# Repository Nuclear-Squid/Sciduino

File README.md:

# Sciduino

An experiment to replace LabVIEW and NI-DAQ devices by a SciPy + PySide + Arduino stack.

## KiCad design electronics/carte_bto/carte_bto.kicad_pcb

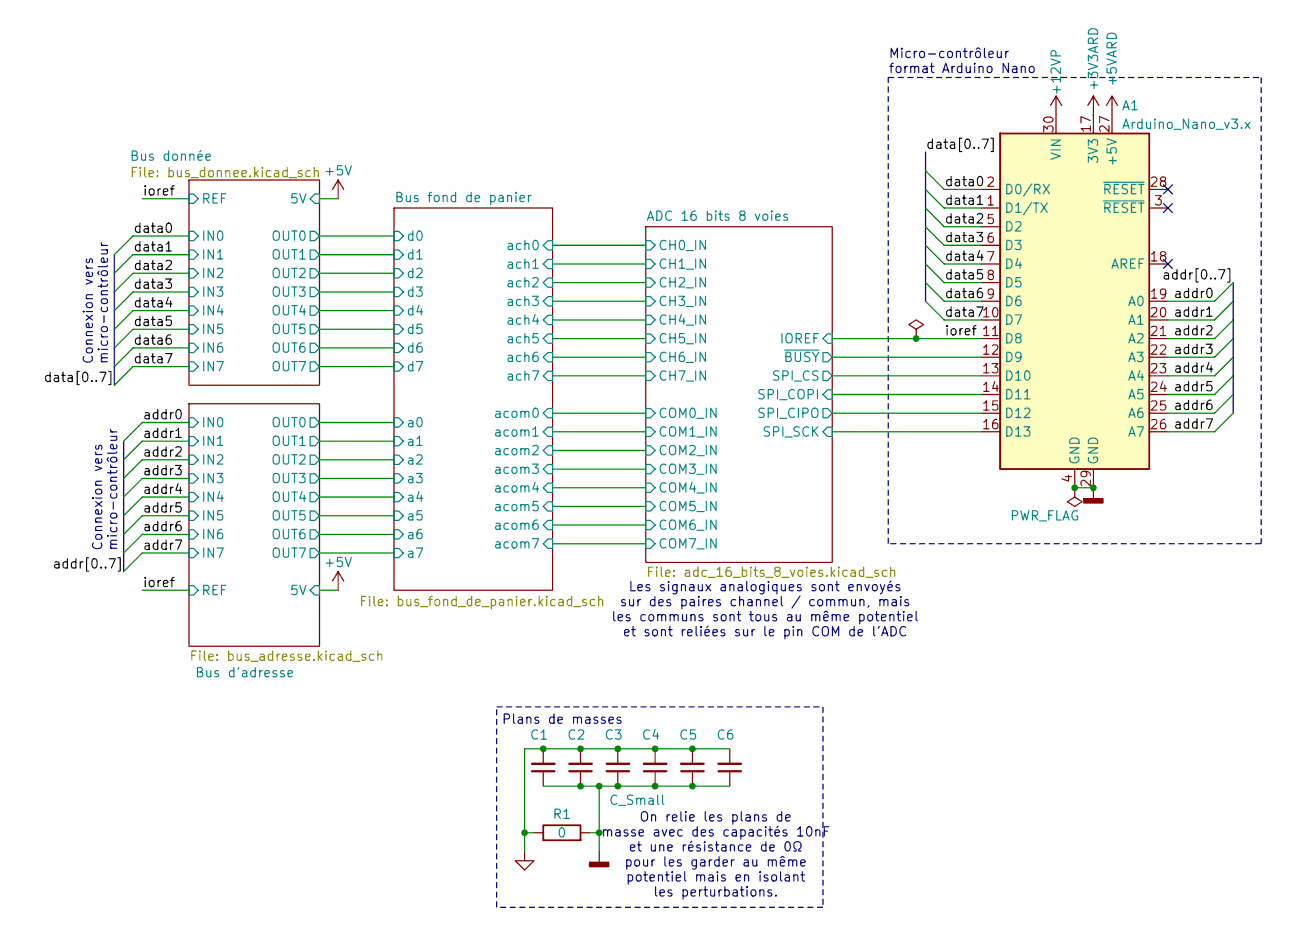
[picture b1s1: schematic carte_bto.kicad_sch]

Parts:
A1: Arduino_Nano_v3.x; Arduino_Nano
C1, C2, C3, C4, C5, C6: C_Small; C_0805_2012Metric_Pad1.18x1.45mm_HandSolder
R1: 0; R_0805_2012Metric_Pad1.20x1.40mm_HandSolder

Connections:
+3V3ARD: A1.17 (3V3)
+5VARD: A1.27 (+5V); also elsewhere on the board
+12VP: A1.30 (VIN); also elsewhere on the board
/ADC 16 bits 8 voies/SPI_CIPO: A1.15 (D12); also elsewhere on the board
/ADC 16 bits 8 voies/SPI_COPI: A1.14 (D11); also elsewhere on the board
/ADC 16 bits 8 voies/SPI_CS: A1.13 (D10); also elsewhere on the board
/ADC 16 bits 8 voies/SPI_SCK: A1.16 (D13); also elsewhere on the board
/ADC 16 bits 8 voies/~BUSY: A1.12 (D9); also elsewhere on the board
/addr0: A1.19 (A0); also elsewhere on the board
/addr1: A1.20 (A1); also elsewhere on the board
/addr2: A1.21 (A2); also elsewhere on the board
/addr3: A1.22 (A3); also elsewhere on the board
/addr4: A1.23 (A4); also elsewhere on the board
/addr5: A1.24 (A5); also elsewhere on the board
/addr6: A1.25 (A6); also elsewhere on the board
/addr7: A1.26 (A7); also elsewhere on the board
/data0: A1.2 (D0/RX); also elsewhere on the board
/data1: A1.1 (D1/TX); also elsewhere on the board
/data2: A1.5 (D2); also elsewhere on the board
/data3: A1.6 (D3); also elsewhere on the board
/data4: A1.7 (D4); also elsewhere on the board
/data5: A1.8 (D5); also elsewhere on the board
/data6: A1.9 (D6); also elsewhere on the board
/data7: A1.10 (D7); also elsewhere on the board
/ioref: A1.11 (D8); also elsewhere on the board
GND1: C1.2, C2.2, C3.2, C4.2, C5.2, C6.2, R1.1; also elsewhere on the board
GND2: A1.4 (GND), A1.29 (GND), C1.1, C2.1, C3.1, C4.1, C5.1, C6.1, R1.2; also elsewhere on the board

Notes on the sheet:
Connexion vers micro-contrôleur
Micro-contrôleur format Arduino Nano
Plans de masses
Les signaux analogiques sont envoyés sur des paires channel / commun, mais les communs sont tous au même potentiel et sont reliées sur le pin COM de l’ADC
On relie les plans de masse avec des capacités 10nF et une résistance de 0Ω pour les garder au même potentiel mais en isolant les perturbations.

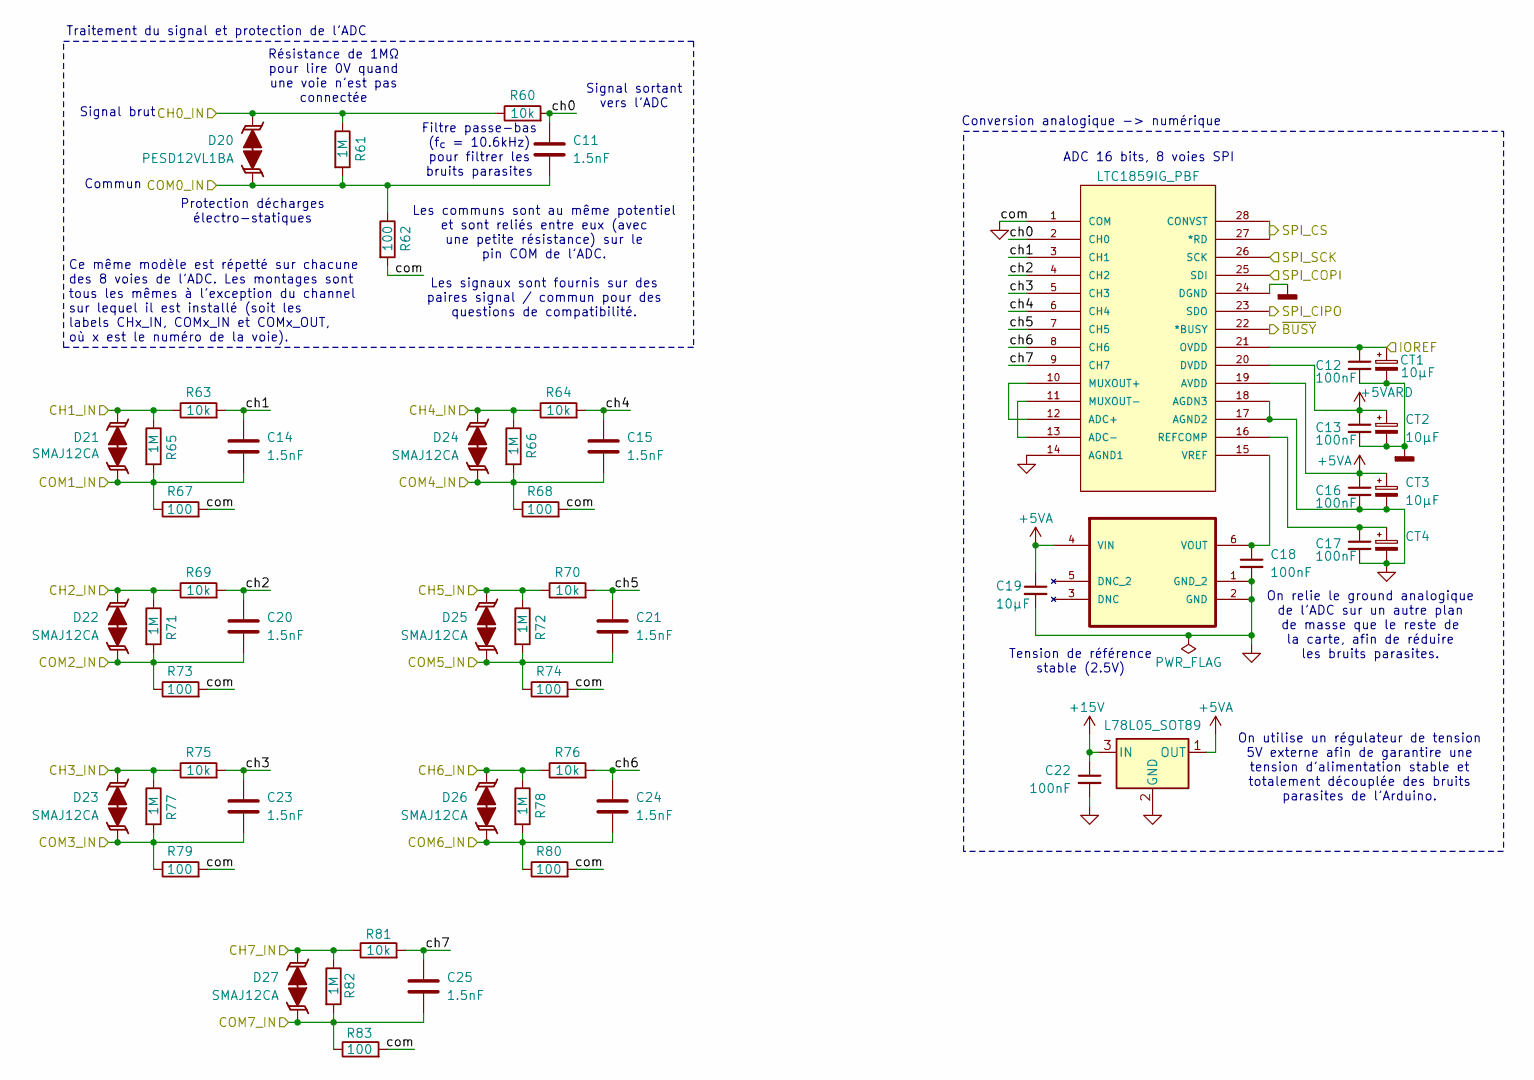
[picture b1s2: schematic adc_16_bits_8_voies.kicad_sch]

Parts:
C11, C14, C15, C20, C21, C23, C24, C25: 1.5nF; C_0805_2012Metric_Pad1.18x1.45mm_HandSolder
C12, C13, C16, C17, C18, C22: 100nF; C_0805_2012Metric_Pad1.18x1.45mm_HandSolder
C19: 10µF; C_0805_2012Metric_Pad1.18x1.45mm_HandSolder
CT1, CT2, CT3, CT4: 10µF; CP_EIA-2012-12_Kemet-R
D20: PESD12VL1BA; D_SOD-323_HandSoldering
D21, D22, D23, D24, D25, D26, D27: SMAJ12CA; D_SOD-323_HandSoldering
R60, R63, R64, R69, R70, R75, R76, R81: 10k; R_0805_2012Metric_Pad1.20x1.40mm_HandSolder
R61, R65, R66, R71, R72, R77, R78, R82: 1M; R_0805_2012Metric_Pad1.20x1.40mm_HandSolder
R62, R67, R68, R73, R74, R79, R80, R83: 100; R_0805_2012Metric_Pad1.20x1.40mm_HandSolder
U3: LTC1859IG_PBF; SSOP-28_G; MANUFACTURER_PART_NUMBER ltc1859ig
U4: LT6654AIS6-2.5_TRPBF; SOT95P280X100-6N; MPN LT6654BHS6-5#TRMPBF
U5: L78L05_SOT89; SOT-89-3_Handsoldering

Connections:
+5VA: C16.1, C19.1, CT3.1, U3.19 (AVDD), U4.4 (VIN), U5.1 (OUT)
+5VARD: C13.1, CT2.1, U3.20 (DVDD); also elsewhere on the board
+15V: C22.1, U5.3 (IN); also elsewhere on the board
/ADC 16 bits 8 voies/CH0_IN: D20.2 (A2), R60.1, R61.1; also elsewhere on the board
/ADC 16 bits 8 voies/CH1_IN: D21.2 (A2), R63.1, R65.1; also elsewhere on the board
/ADC 16 bits 8 voies/CH2_IN: D22.2 (A2), R69.1, R71.1; also elsewhere on the board
/ADC 16 bits 8 voies/CH3_IN: D23.2 (A2), R75.1, R77.1; also elsewhere on the board
/ADC 16 bits 8 voies/CH4_IN: D24.2 (A2), R64.1, R66.1; also elsewhere on the board
/ADC 16 bits 8 voies/CH5_IN: D25.2 (A2), R70.1, R72.1; also elsewhere on the board
/ADC 16 bits 8 voies/CH6_IN: D26.2 (A2), R76.1, R78.1; also elsewhere on the board
/ADC 16 bits 8 voies/CH7_IN: D27.2 (A2), R81.1, R82.1; also elsewhere on the board
/ADC 16 bits 8 voies/COM0_IN: C11.2, D20.1 (A1), R61.2, R62.1; also elsewhere on the board
/ADC 16 bits 8 voies/COM1_IN: C14.2, D21.1 (A1), R65.2, R67.1; also elsewhere on the board
/ADC 16 bits 8 voies/COM2_IN: C20.2, D22.1 (A1), R71.2, R73.1; also elsewhere on the board
/ADC 16 bits 8 voies/COM3_IN: C23.2, D23.1 (A1), R77.2, R79.1; also elsewhere on the board
/ADC 16 bits 8 voies/COM4_IN: C15.2, D24.1 (A1), R66.2, R68.1; also elsewhere on the board
/ADC 16 bits 8 voies/COM5_IN: C21.2, D25.1 (A1), R72.2, R74.1; also elsewhere on the board
/ADC 16 bits 8 voies/COM6_IN: C24.2, D26.1 (A1), R78.2, R80.1; also elsewhere on the board
/ADC 16 bits 8 voies/COM7_IN: C25.2, D27.1 (A1), R82.2, R83.1; also elsewhere on the board
/ADC 16 bits 8 voies/SPI_CIPO: U3.23 (SDO); also elsewhere on the board
/ADC 16 bits 8 voies/SPI_COPI: U3.25 (SDI); also elsewhere on the board
/ADC 16 bits 8 voies/SPI_CS: U3.27 (*RD), U3.28 (CONVST); also elsewhere on the board
/ADC 16 bits 8 voies/SPI_SCK: U3.26 (SCK); also elsewhere on the board
/ADC 16 bits 8 voies/ch0: C11.1, R60.2, U3.2 (CH0)
/ADC 16 bits 8 voies/ch1: C14.1, R63.2, U3.3 (CH1)
/ADC 16 bits 8 voies/ch2: C20.1, R69.2, U3.4 (CH2)
/ADC 16 bits 8 voies/ch3: C23.1, R75.2, U3.5 (CH3)
/ADC 16 bits 8 voies/ch4: C15.1, R64.2, U3.6 (CH4)
/ADC 16 bits 8 voies/ch5: C21.1, R70.2, U3.7 (CH5)
/ADC 16 bits 8 voies/ch6: C24.1, R76.2, U3.8 (CH6)
/ADC 16 bits 8 voies/ch7: C25.1, R81.2, U3.9 (CH7)
/ADC 16 bits 8 voies/~BUSY: U3.22 (*BUSY); also elsewhere on the board
/ioref: C12.1, CT1.1, U3.21 (OVDD); also elsewhere on the board
GND1: C16.2, C17.2, C18.2, C19.2, C22.2, CT3.2, CT4.2, R62.2, R67.2, R68.2, R73.2, R74.2, R79.2, R80.2, R83.2, U3.1 (COM), U3.14 (AGND1), U3.17 (AGND2), U3.18 (AGDN3), U4.1 (GND_2), U4.2 (GND), U5.2 (GND); also elsewhere on the board
GND2: C12.2, C13.2, CT1.2, CT2.2, U3.24 (DGND); also elsewhere on the board
unnamed: U3.10 (MUXOUT+), U3.12 (ADC+)
unnamed: U3.11 (MUXOUT-), U3.13 (ADC-)
unnamed: C17.1, CT4.1, U3.16 (REFCOMP)
unnamed: C18.1, U3.15 (VREF), U4.6 (VOUT)

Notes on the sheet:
Signal sortant vers l’ADC
Traitement du signal et protection de l’ADC
On utilise un régulateur de tension 5V externe afin de garantire une tension d’alimentation stable et totalement découplée des bruits parasites de l’Arduino.
Résistance de 1MΩ pour lire 0V quand une voie n’est pas connectée
ADC 16 bits, 8 voies SPI
Tension de référence stable (2.5V)
Les communs sont au même potentiel et sont reliés entre eux (avec une petite résistance) sur le pin COM de l’ADC. Les signaux sont fournis sur des paires signal / commun pour des questions de compatibilité.
Filtre passe-bas (f_{c} = 10.6kHz) pour filtrer les bruits parasites
Ce même modèle est répetté sur chacune des 8 voies de l’ADC. Les montages sont tous les mêmes à l’exception du channel sur lequel il est installé (soit les labels CHx_IN, COMx_IN et COMx_OUT, où x est le numéro de la voie).
Signal brut
Commun
Conversion analogique -> numérique
On relie le ground analogique de l’ADC sur un autre plan de masse que le reste de la carte, afin de réduire les bruits parasites.
Protection décharges électro-statiques

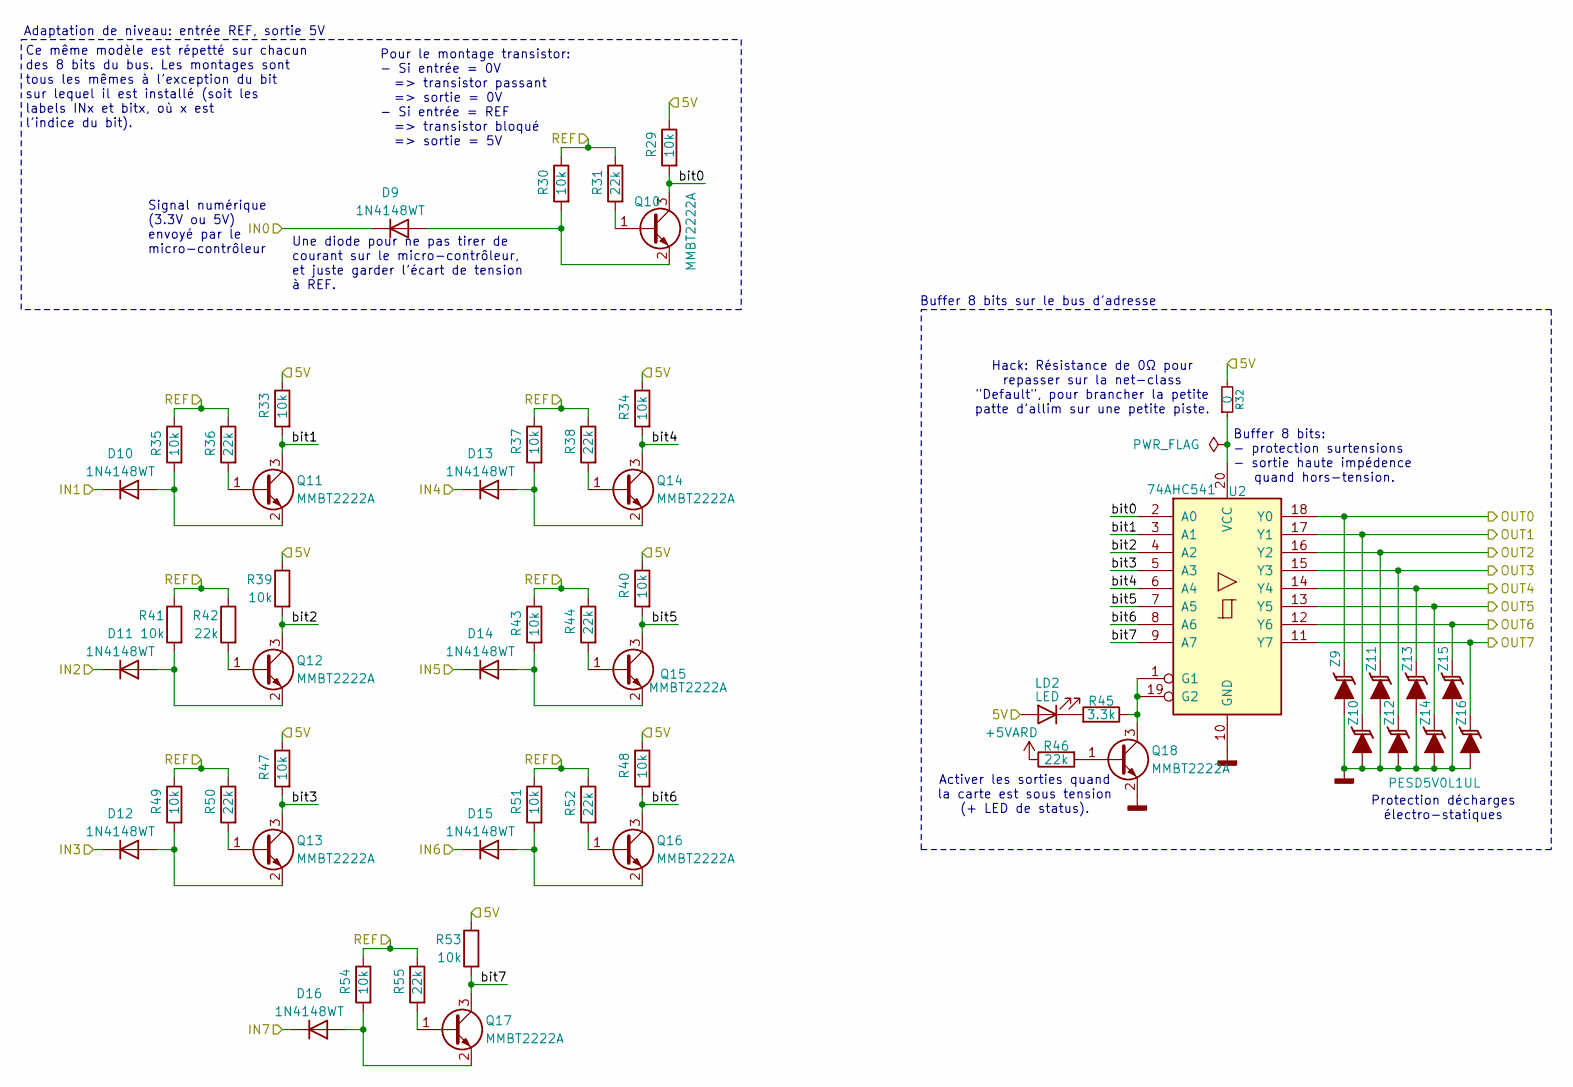
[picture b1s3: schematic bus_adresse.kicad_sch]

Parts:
D9, D10, D11, D12, D13, D14, D15, D16: 1N4148WT; D_SOD-523
LD2: LED; LED_0805_2012Metric_Pad1.15x1.40mm_HandSolder
Q10, Q11, Q12, Q13, Q14, Q15, Q16, Q17, Q18: MMBT2222A; SOT-23_Handsoldering
R29, R30, R33, R34, R35, R37, R39, R40, R41, R43, R47, R48, R49, R51, R53, R54: 10k; R_0805_2012Metric_Pad1.20x1.40mm_HandSolder
R31, R36, R38, R42, R44, R46, R50, R52, R55: 22k; R_0805_2012Metric_Pad1.20x1.40mm_HandSolder
R32: 0; R_0805_2012Metric_Pad1.20x1.40mm_HandSolder
R45: 3.3k; R_0805_2012Metric_Pad1.20x1.40mm_HandSolder
U2: 74AHC541; SOIC-20W_7.5x12.8mm_P1.27mm
Z9, Z10, Z11, Z12, Z13, Z14, Z15, Z16: PESD5V0L1UL; D_SOD-882_DFN1006-2_TVS

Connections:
+5V: LD2.2 (A), R29.1, R32.2, R33.1, R34.1, R39.1, R40.1, R47.1, R48.1, R53.1; also elsewhere on the board
+5VARD: R46.1; also elsewhere on the board
/Bus d’adresse/OUT0: U2.18 (Y0), Z9.1 (K); also elsewhere on the board
/Bus d’adresse/OUT1: U2.17 (Y1), Z10.1 (K); also elsewhere on the board
/Bus d’adresse/OUT2: U2.16 (Y2), Z11.1 (K); also elsewhere on the board
/Bus d’adresse/OUT3: U2.15 (Y3), Z12.1 (K); also elsewhere on the board
/Bus d’adresse/OUT4: U2.14 (Y4), Z13.1 (K); also elsewhere on the board
/Bus d’adresse/OUT5: U2.13 (Y5), Z14.1 (K); also elsewhere on the board
/Bus d’adresse/OUT6: U2.12 (Y6), Z15.1 (K); also elsewhere on the board
/Bus d’adresse/OUT7: U2.11 (Y7), Z16.1 (K); also elsewhere on the board
/Bus d’adresse/bit0: Q10.3 (C), R29.2, U2.2 (A0)
/Bus d’adresse/bit1: Q11.3 (C), R33.2, U2.3 (A1)
/Bus d’adresse/bit2: Q12.3 (C), R39.2, U2.4 (A2)
/Bus d’adresse/bit3: Q13.3 (C), R47.2, U2.5 (A3)
/Bus d’adresse/bit4: Q14.3 (C), R34.2, U2.6 (A4)
/Bus d’adresse/bit5: Q15.3 (C), R40.2, U2.7 (A5)
/Bus d’adresse/bit6: Q16.3 (C), R48.2, U2.8 (A6)
/Bus d’adresse/bit7: Q17.3 (C), R53.2, U2.9 (A7)
/addr0: D9.1 (K); also elsewhere on the board
/addr1: D10.1 (K); also elsewhere on the board
/addr2: D11.1 (K); also elsewhere on the board
/addr3: D12.1 (K); also elsewhere on the board
/addr4: D13.1 (K); also elsewhere on the board
/addr5: D14.1 (K); also elsewhere on the board
/addr6: D15.1 (K); also elsewhere on the board
/addr7: D16.1 (K); also elsewhere on the board
/ioref: R30.1, R31.1, R35.1, R36.1, R37.1, R38.1, R41.1, R42.1, R43.1, R44.1, R49.1, R50.1, R51.1, R52.1, R54.1, R55.1; also elsewhere on the board
GND2: Q18.2 (E), U2.10 (GND), Z9.2 (A), Z10.2 (A), Z11.2 (A), Z12.2 (A), Z13.2 (A), Z14.2 (A), Z15.2 (A), Z16.2 (A); also elsewhere on the board
unnamed: D9.2 (A), Q10.2 (E), R30.2
unnamed: D10.2 (A), Q11.2 (E), R35.2
unnamed: D11.2 (A), Q12.2 (E), R41.2
unnamed: D12.2 (A), Q13.2 (E), R49.2
unnamed: D13.2 (A), Q14.2 (E), R37.2
unnamed: D14.2 (A), Q15.2 (E), R43.2
unnamed: D15.2 (A), Q16.2 (E), R51.2
unnamed: D16.2 (A), Q17.2 (E), R54.2
unnamed: LD2.1 (K), R45.2
unnamed: Q10.1 (B), R31.2
unnamed: Q11.1 (B), R36.2
unnamed: Q12.1 (B), R42.2
unnamed: Q13.1 (B), R50.2
unnamed: Q14.1 (B), R38.2
unnamed: Q15.1 (B), R44.2
unnamed: Q16.1 (B), R52.2
unnamed: Q17.1 (B), R55.2
unnamed: Q18.1 (B), R46.2
unnamed: Q18.3 (C), R45.1, U2.1 (G1), U2.19 (G2)
unnamed: R32.1, U2.20 (VCC)

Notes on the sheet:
Buffer 8 bits: - protection surtensions - sortie haute impédence quand hors-tension.
Une diode pour ne pas tirer de courant sur le micro-contrôleur, et juste garder l’écart de tension à REF.
Ce même modèle est répetté sur chacun des 8 bits du bus. Les montages sont tous les mêmes à l’exception du bit sur lequel il est installé (soit les labels INx et bitx, où x est l’indice du bit).
Activer les sorties quand la carte est sous tension (+ LED de status).
Adaptation de niveau: entrée REF, sortie 5V
Hack: Résistance de 0Ω pour repasser sur la net-class "Default", pour brancher la petite patte d’allim sur une petite piste.
Signal numérique (3.3V ou 5V) envoyé par le micro-contrôleur
Buffer 8 bits sur le bus d’adresse
Pour le montage transistor: - Si entrée = 0V => transistor passant => sortie = 0V - Si entrée = REF => transistor bloqué => sortie = 5V
Protection décharges électro-statiques

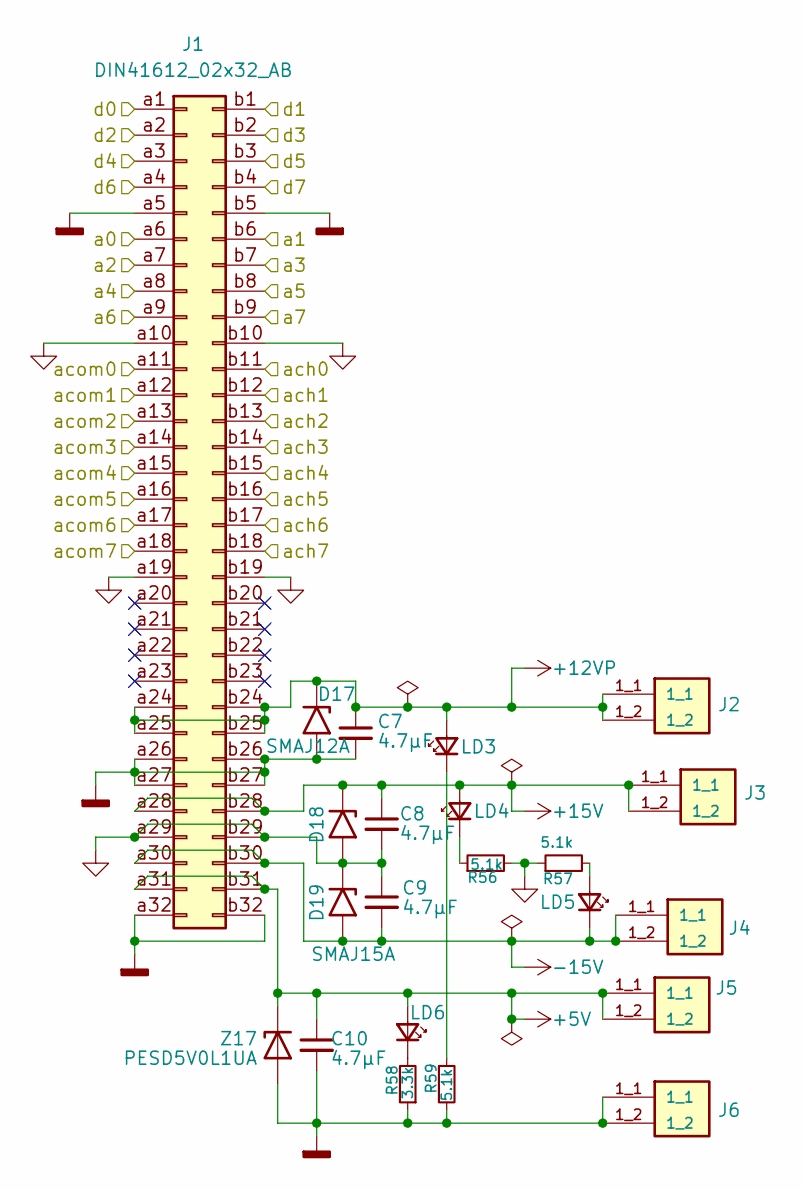
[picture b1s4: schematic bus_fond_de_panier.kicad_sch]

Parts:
C7, C8, C9, C10: 4.7µF; C_0805_2012Metric_Pad1.18x1.45mm_HandSolder
D17: SMAJ12A; D_SOD-323_HandSoldering
D18, D19: SMAJ15A; D_SOD-323_HandSoldering
J1: DIN41612_02x32_AB; DIN41612_B_2x32_Male_Horizontal_THT
J2, J3, J4, J5, J6: Conn_01x01; HIRSCHMANN_930224100
LD3, LD4, LD5, LD6: LED_Small; LED_0805_2012Metric_Pad1.15x1.40mm_HandSolder
R56, R57, R59: 5.1k; R_0805_2012Metric_Pad1.20x1.40mm_HandSolder
R58: 3.3k; R_0805_2012Metric_Pad1.20x1.40mm_HandSolder
Z17: PESD5V0L1UA; D_SOD-323_HandSoldering

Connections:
+5V: C10.1, J1.a31, J1.b31, J5.1_1, J5.1_2, LD6.2 (A), Z17.1 (K); also elsewhere on the board
+12VP: C7.1, D17.1 (A1), J1.a24, J1.a25, J1.b24, J1.b25, J2.1_1, J2.1_2, LD3.2 (A); also elsewhere on the board
+15V: C8.1, D18.1 (A1), J1.a28, J1.b28, J3.1_1, J3.1_2, LD4.2 (A); also elsewhere on the board
-15V: C9.2, D19.2 (A2), J1.a30, J1.b30, J4.1_1, J4.1_2, LD5.1 (K)
/ADC 16 bits 8 voies/CH0_IN: J1.b11; also elsewhere on the board
/ADC 16 bits 8 voies/CH1_IN: J1.b12; also elsewhere on the board
/ADC 16 bits 8 voies/CH2_IN: J1.b13; also elsewhere on the board
/ADC 16 bits 8 voies/CH3_IN: J1.b14; also elsewhere on the board
/ADC 16 bits 8 voies/CH4_IN: J1.b15; also elsewhere on the board
/ADC 16 bits 8 voies/CH5_IN: J1.b16; also elsewhere on the board
/ADC 16 bits 8 voies/CH6_IN: J1.b17; also elsewhere on the board
/ADC 16 bits 8 voies/CH7_IN: J1.b18; also elsewhere on the board
/ADC 16 bits 8 voies/COM0_IN: J1.a11; also elsewhere on the board
/ADC 16 bits 8 voies/COM1_IN: J1.a12; also elsewhere on the board
/ADC 16 bits 8 voies/COM2_IN: J1.a13; also elsewhere on the board
/ADC 16 bits 8 voies/COM3_IN: J1.a14; also elsewhere on the board
/ADC 16 bits 8 voies/COM4_IN: J1.a15; also elsewhere on the board
/ADC 16 bits 8 voies/COM5_IN: J1.a16; also elsewhere on the board
/ADC 16 bits 8 voies/COM6_IN: J1.a17; also elsewhere on the board
/ADC 16 bits 8 voies/COM7_IN: J1.a18; also elsewhere on the board
/Bus donnée/OUT0: J1.a1; also elsewhere on the board
/Bus donnée/OUT1: J1.b1; also elsewhere on the board
/Bus donnée/OUT2: J1.a2; also elsewhere on the board
/Bus donnée/OUT3: J1.b2; also elsewhere on the board
/Bus donnée/OUT4: J1.a3; also elsewhere on the board
/Bus donnée/OUT5: J1.b3; also elsewhere on the board
/Bus donnée/OUT6: J1.a4; also elsewhere on the board
/Bus donnée/OUT7: J1.b4; also elsewhere on the board
/Bus d’adresse/OUT0: J1.a6; also elsewhere on the board
/Bus d’adresse/OUT1: J1.b6; also elsewhere on the board
/Bus d’adresse/OUT2: J1.a7; also elsewhere on the board
/Bus d’adresse/OUT3: J1.b7; also elsewhere on the board
/Bus d’adresse/OUT4: J1.a8; also elsewhere on the board
/Bus d’adresse/OUT5: J1.b8; also elsewhere on the board
/Bus d’adresse/OUT6: J1.a9; also elsewhere on the board
/Bus d’adresse/OUT7: J1.b9; also elsewhere on the board
GND1: C8.2, C9.1, D18.2 (A2), D19.1 (A1), J1.a10, J1.a19, J1.a29, J1.b10, J1.b19, J1.b29, R56.2, R57.1; also elsewhere on the board
GND2: C7.2, C10.2, D17.2 (A2), J1.a5, J1.a26, J1.a27, J1.a32, J1.b5, J1.b26, J1.b27, J1.b32, J6.1_1, J6.1_2, R58.1, R59.2, Z17.2 (A); also elsewhere on the board
unnamed: LD3.1 (K), R59.1
unnamed: LD4.1 (K), R56.1
unnamed: LD5.2 (A), R57.2
unnamed: LD6.1 (K), R58.2

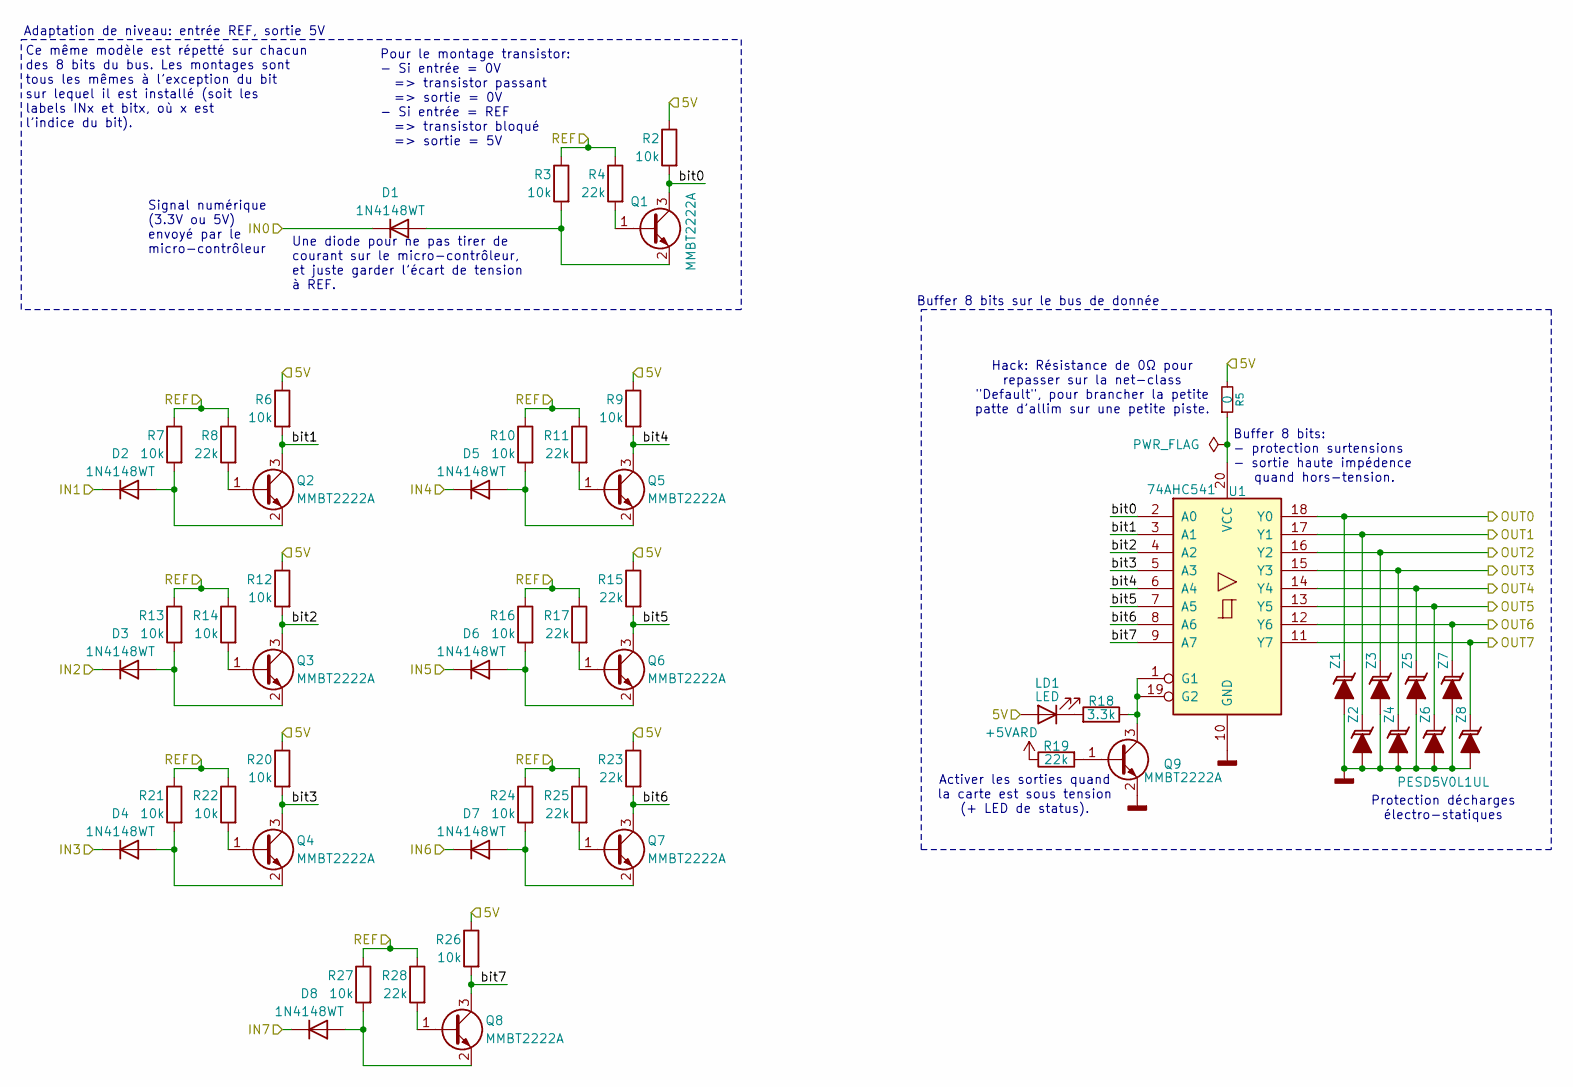
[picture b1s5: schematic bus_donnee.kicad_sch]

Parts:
D1, D2, D3, D4, D5, D6, D7, D8: 1N4148WT; D_SOD-523
LD1: LED; LED_0805_2012Metric_Pad1.15x1.40mm_HandSolder
Q1, Q2, Q3, Q4, Q5, Q6, Q7, Q8, Q9: MMBT2222A; SOT-23_Handsoldering
R2, R3, R6, R7, R9, R10, R12, R13, R14, R16, R20, R21, R22, R24, R26, R27: 10k; R_0805_2012Metric_Pad1.20x1.40mm_HandSolder
R4, R8, R11, R15, R17, R19, R23, R25, R28: 22k; R_0805_2012Metric_Pad1.20x1.40mm_HandSolder
R5: 0; R_0805_2012Metric_Pad1.20x1.40mm_HandSolder
R18: 3.3k; R_0805_2012Metric_Pad1.20x1.40mm_HandSolder
U1: 74AHC541; SOIC-20W_7.5x12.8mm_P1.27mm
Z1, Z2, Z3, Z4, Z5, Z6, Z7, Z8: PESD5V0L1UL; D_SOD-882_DFN1006-2_TVS

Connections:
+5V: LD1.2 (A), R2.1, R5.2, R6.1, R9.1, R12.1, R15.1, R20.1, R23.1, R26.1; also elsewhere on the board
+5VARD: R19.1; also elsewhere on the board
/Bus donnée/OUT0: U1.18 (Y0), Z1.1 (K); also elsewhere on the board
/Bus donnée/OUT1: U1.17 (Y1), Z2.1 (K); also elsewhere on the board
/Bus donnée/OUT2: U1.16 (Y2), Z3.1 (K); also elsewhere on the board
/Bus donnée/OUT3: U1.15 (Y3), Z4.1 (K); also elsewhere on the board
/Bus donnée/OUT4: U1.14 (Y4), Z5.1 (K); also elsewhere on the board
/Bus donnée/OUT5: U1.13 (Y5), Z6.1 (K); also elsewhere on the board
/Bus donnée/OUT6: U1.12 (Y6), Z7.1 (K); also elsewhere on the board
/Bus donnée/OUT7: U1.11 (Y7), Z8.1 (K); also elsewhere on the board
/Bus donnée/bit0: Q1.3 (C), R2.2, U1.2 (A0)
/Bus donnée/bit1: Q2.3 (C), R6.2, U1.3 (A1)
/Bus donnée/bit2: Q3.3 (C), R12.2, U1.4 (A2)
/Bus donnée/bit3: Q4.3 (C), R20.2, U1.5 (A3)
/Bus donnée/bit4: Q5.3 (C), R9.2, U1.6 (A4)
/Bus donnée/bit5: Q6.3 (C), R15.2, U1.7 (A5)
/Bus donnée/bit6: Q7.3 (C), R23.2, U1.8 (A6)
/Bus donnée/bit7: Q8.3 (C), R26.2, U1.9 (A7)
/data0: D1.1 (K); also elsewhere on the board
/data1: D2.1 (K); also elsewhere on the board
/data2: D3.1 (K); also elsewhere on the board
/data3: D4.1 (K); also elsewhere on the board
/data4: D5.1 (K); also elsewhere on the board
/data5: D6.1 (K); also elsewhere on the board
/data6: D7.1 (K); also elsewhere on the board
/data7: D8.1 (K); also elsewhere on the board
/ioref: R3.1, R4.1, R7.1, R8.1, R10.1, R11.1, R13.1, R14.1, R16.1, R17.1, R21.1, R22.1, R24.1, R25.1, R27.1, R28.1; also elsewhere on the board
GND2: Q9.2 (E), U1.10 (GND), Z1.2 (A), Z2.2 (A), Z3.2 (A), Z4.2 (A), Z5.2 (A), Z6.2 (A), Z7.2 (A), Z8.2 (A); also elsewhere on the board
unnamed: D1.2 (A), Q1.2 (E), R3.2
unnamed: D2.2 (A), Q2.2 (E), R7.2
unnamed: D3.2 (A), Q3.2 (E), R13.2
unnamed: D4.2 (A), Q4.2 (E), R21.2
unnamed: D5.2 (A), Q5.2 (E), R10.2
unnamed: D6.2 (A), Q6.2 (E), R16.2
unnamed: D7.2 (A), Q7.2 (E), R24.2
unnamed: D8.2 (A), Q8.2 (E), R27.2
unnamed: LD1.1 (K), R18.2
unnamed: Q1.1 (B), R4.2
unnamed: Q2.1 (B), R8.2
unnamed: Q3.1 (B), R14.2
unnamed: Q4.1 (B), R22.2
unnamed: Q5.1 (B), R11.2
unnamed: Q6.1 (B), R17.2
unnamed: Q7.1 (B), R25.2
unnamed: Q8.1 (B), R28.2
unnamed: Q9.1 (B), R19.2
unnamed: Q9.3 (C), R18.1, U1.1 (G1), U1.19 (G2)
unnamed: R5.1, U1.20 (VCC)

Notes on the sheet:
Adaptation de niveau: entrée REF, sortie 5V
Buffer 8 bits sur le bus de donnée
Buffer 8 bits: - protection surtensions - sortie haute impédence quand hors-tension.
Activer les sorties quand la carte est sous tension (+ LED de status).
Signal numérique (3.3V ou 5V) envoyé par le micro-contrôleur
Protection décharges électro-statiques
Ce même modèle est répetté sur chacun des 8 bits du bus. Les montages sont tous les mêmes à l’exception du bit sur lequel il est installé (soit les labels INx et bitx, où x est l’indice du bit).
Une diode pour ne pas tirer de courant sur le micro-contrôleur, et juste garder l’écart de tension à REF.
Hack: Résistance de 0Ω pour repasser sur la net-class "Default", pour brancher la petite patte d’allim sur une petite piste.
Pour le montage transistor: - Si entrée = 0V => transistor passant => sortie = 0V - Si entrée = REF => transistor bloqué => sortie = 5V

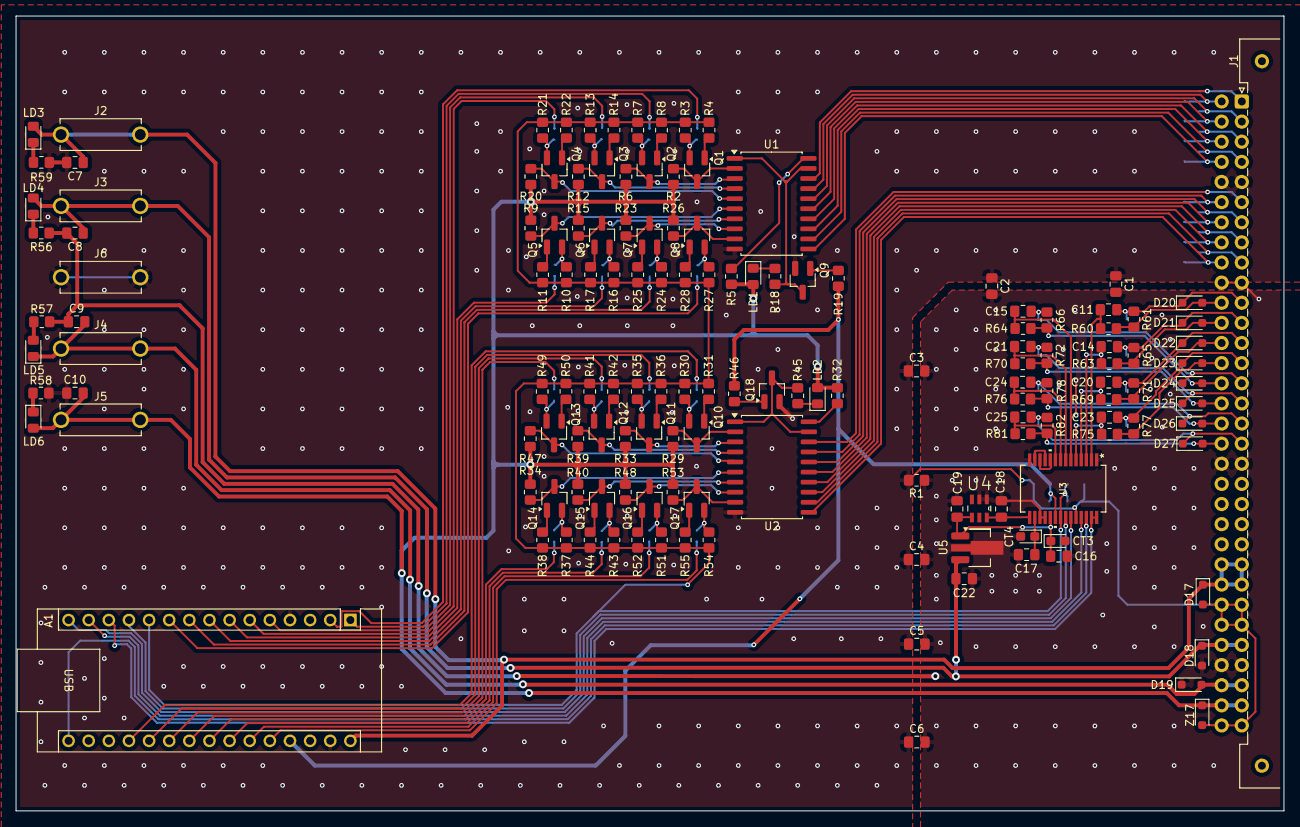
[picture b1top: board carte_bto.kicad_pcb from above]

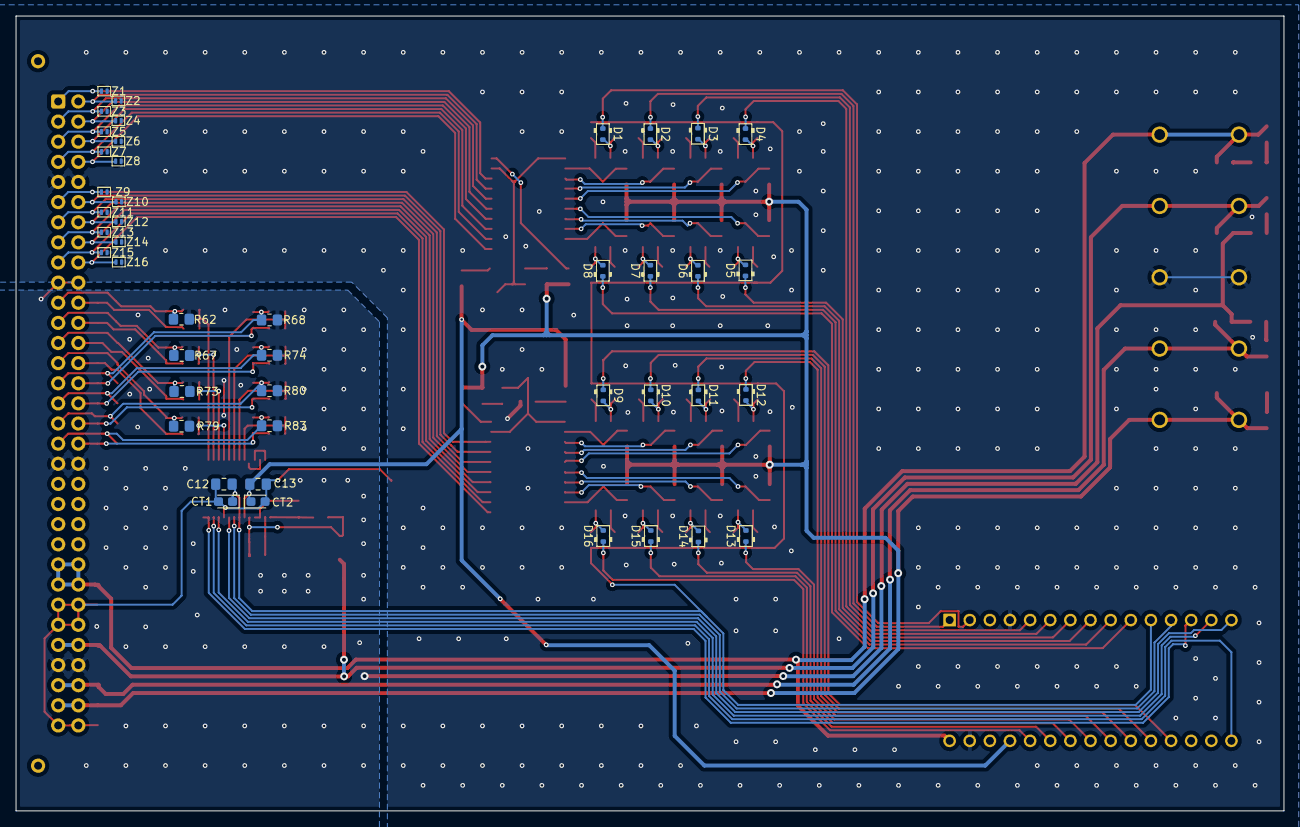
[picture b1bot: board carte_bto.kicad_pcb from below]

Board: 2 copper layers, 160.0 x 100.3 mm, 192 parts (44 on the bottom side), 134 nets.

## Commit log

2025-05-12 Ascii stream + prototype app with measure & burst
2025-05-12 App: removed styling
2025-05-12 Board: imported `TimerInterrupt` library locally.
2025-05-14 Board: added arguments to `:brst` command
2025-05-14 Board: Some refactoring (state machine)
2025-05-14 Board: Renamed `libs` folder to `3rd_parts`.
2025-05-14 App: Proper parameter handling in GUI.
2025-05-14 All: Renamed commands to better fit the SCPI protocol.
2025-05-14 All: Send burst data as raw bytes.
2025-05-14 Board: Added arguments to `:stream` command and send data as raw bytes.
2025-05-16 Board: added command to switch between ascii / binary response format.
2025-05-16 Board: build script can be called from outside folder.
2025-05-16 App: Fixed binary decoding + cleaner code structure.
2025-05-19 App: Update graph in python backend + Wip stream.
2025-05-21 All: Scpino -> Sciduino (+ moved python class to module).
2025-05-27 Wip: Waveform data type.
    Wip: Waveform integration.
2025-05-27 All: handle waveforms from multiple sources.
2025-05-27 Updated dependencies
2025-05-27 Refactored waveforms + ascii parser
    Split waveform into .h and .ino files.
    Board: refactored waveforms + fixed floats in ascii mode.
2025-05-27 Board: Use program memory whenever possible.
2025-05-27 feat(App): Implemented multi input stream + scroll.
2025-06-12 feat(app): MUCH cleaner UI.
2025-06-12 Fixed typo in folder name.
2025-06-17 Wip: communication SPI fonctionnelle avec MAX1300.
2025-06-17 Cleanup
2025-06-17 Basic class for MAX1300.
2025-06-18 Basic abstraction over timer libraries.
2025-06-19 Implemented a simple SPI driver for MAX1300 ADC.
2025-06-19 Removed SPI test Arduino sketch.
2025-06-19 Implemented a simple SPI driver for MAX1300 ADC. (#1)
    * Wip: communication SPI fonctionnelle avec MAX1300.
    * Cleanup
    * Basic class for MAX1300.
    * Basic abstraction over timer libraries.
    * Implemented a simple SPI driver for MAX1300 ADC.
    * Removed SPI test Arduino sketch.
2025-06-19 Quick fix: measure.
2025-06-23 Wip ADC API: analogRead.
2025-06-23 Simple LTC1859 driver.
2025-06-24 Adc: Cleanup and some refactor.
2025-06-24 Easy to configure input range (LTC1859 only, for now).
2025-06-25 Added methods to read a stream or burst using ADC.
2025-06-26 Simple input selection.
2025-06-30 Input selection cleanup / refactor.
2025-06-30 Simple SCPI command concatenation.
2025-07-01 feat: Added channel selection.
2025-07-01 SCPI: handle abbreviated concatenated commands.
2025-07-02 Minimum viable product.
2025-07-02 Fixed binary -> float conversion of LTC1859 using symetrical input ranges.
2025-07-15 Functionnal BTO schematic.
2025-07-15 BTO schematic: cleanup and documentation
2025-07-22 BTO: minor schematic fixes & PCB routing.
    backup
    BTO: Minor fixes on schematic & PCB routing.
2025-07-24 BTO: more fixes & PCB cleanup
2025-07-25 BTO: Better routing.
2025-07-25 BTO: added 0Ω resistors for a net class hack.
2025-07-30 BTO: Changed footprints to handsoldering verions, redid PCB routing
2025-07-30 Updated .gitignore
2025-07-30 Cleanup file tree, removed old unused files.
2025-08-09 Import du taf sur Cryptpad.
2025-08-10 Carte BTO
2025-08-10 choix du matériel
2025-08-10 KiCad
2025-08-10 Corrections mineures
2025-08-10 Stack logicielle
2025-08-10 Mise en œuvre.
2025-08-11 Stack logicielle — liens + proposition de déplacement
2025-08-11 typos
2025-08-11 RPi Pico
2025-08-11 Contexte / Technologies
2025-08-11 Reorganisation: doc
2025-08-11 Reorganisation: `src` folder.
2025-08-11 Replaced `TimerInterrupt` lib by `TimerInterrupt_Generic` as a submodule.
2025-08-11 Documentation
    * Import du taf sur Cryptpad.
    * Carte BTO
    * choix du matériel
    * KiCad
    * Corrections mineures
    * Stack logicielle
2025-08-11 Added a README.
2025-08-11 Added a License (GPL v3).
2025-08-11 Rapport de stage.
    trying to fix the first item
    ToC
    ToC
    ToC
    ToC
    Just found out there *was* already an outline that makes a perfect ToC.
2025-08-11 Table of contents. (#3)
    * Documentation
    * Import du taf sur Cryptpad.
    * Carte BTO
    * choix du matériel
    * KiCad
    * Corrections mineures
2025-08-11 Cleanup.
2025-08-11 Fixed git submodule.
2025-08-11 Updated gitignore (+ removed __pycache__)
2025-08-11 Typst stylesheet.
2025-08-11 line gradient
2025-08-11 metadata
2025-08-11 list layout + ToC
2025-08-11 table layout
2025-08-11 typo
2025-08-12 cadence d’échantillonnage
2025-08-12 Report (#4)
    * Cleanup.
    * Typst stylesheet.
    * line gradient
    * typos
    * typo
    * table layout
2025-08-13 Zabelle
2025-08-13 objectifs
2025-08-13 nitpicks
2025-08-13 liens RetEx
2025-08-13 QML + SciPy
2025-08-13 répétition
2025-08-13 Report (#5)
    * typo
    * Zabelle
    * objectifs
    * nitpicks
    * liens RetEx
    * QML + SciPy
2025-08-13 addressing review comments
2025-08-13 ToC update
2025-08-13 add the confidentiality note
2025-08-13 better header and footer
2025-08-14 first page
2025-08-14 Logos Polytech et RBI.
2025-08-14 font-size
2025-08-14 abstract
2025-08-14 colophon + abstract
2025-08-14 slightly smaller fonts
2025-08-15 Corrections on PIOs and electronics validation.
2025-08-15 Better screenshots
2025-08-16 references
2025-08-16 typos (BEP)
2025-08-16 Dionysos : rp2040 + 1 MHz
2025-08-16 PIO corrections + dev environment.
2025-08-16 Dionysos: "mise en œuvre" section + minor fixes.
2025-08-16 Dionysos: perspectives (+ removed useless graph)
2025-08-25 Fixed git submodule url (ssh -> https).
2025-08-26 Quick fix: Timers for Arduino Nano Every.
2025-08-26 Quick fix: typos + editor config.
